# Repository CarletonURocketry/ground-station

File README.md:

# CUInSpace Telemetry Server

This software is a command line tool for retrieving UART data via serial from the CUInSpace
[ground station board][ground-station-board] and parsing it into readable data which is served via websocket for the
[ground-station-ui][ground-station-ui] live telemetry dashboard.

## Quick Start
Before starting, ensure you have Python 3.11+ installed and the CP210x driver for the homemade ground-station board UART
connection. This is not necessary if using the PICTail Daughter Board.

- Download the latest release
- Navigate to the project directory from the terminal
- Run `pip install -r requirements.txt`
- Run `py main.py -h` for a list of commands

Note that the ground station device should be connected before starting the telemetry server in order to receive an
accurate list of available serial ports.

## Further Reading
Please see the [GitHub Wiki][wiki] for further documentation on how to set up and run the telemetry server.

## Contribution
To contribute to this project, please view the contribution guidelines in the project's GitHub Wiki. Note that
contributions are currently limited to *Carleton University students or CUInSpace members*.

### Authors
- Samuel Dewan
- Thomas Selwyn
- Matteo Golin
- Arsalan Syed

<!--Links-->
[ground-station-board]: https://github.com/CarletonURocketry/avionics-hardware/pull/18
[ground-station-ui]: https://github.com/CarletonURocketry/ground-station-ui
[wiki]: https://github.com/CarletonURocketry/ground-station/wiki

## Installation
```
python3 -m venv .venv
```

```
source .venv/bin/activate
```

```
pip install -r requirements.txt
```

```
pip install -e .
```

## Running the ground station
```
python main.py
```

## Running the radio tests
### To receive
```
python range-test/receive.py
```
### To transmit
```
python range-test/transmit.py
```

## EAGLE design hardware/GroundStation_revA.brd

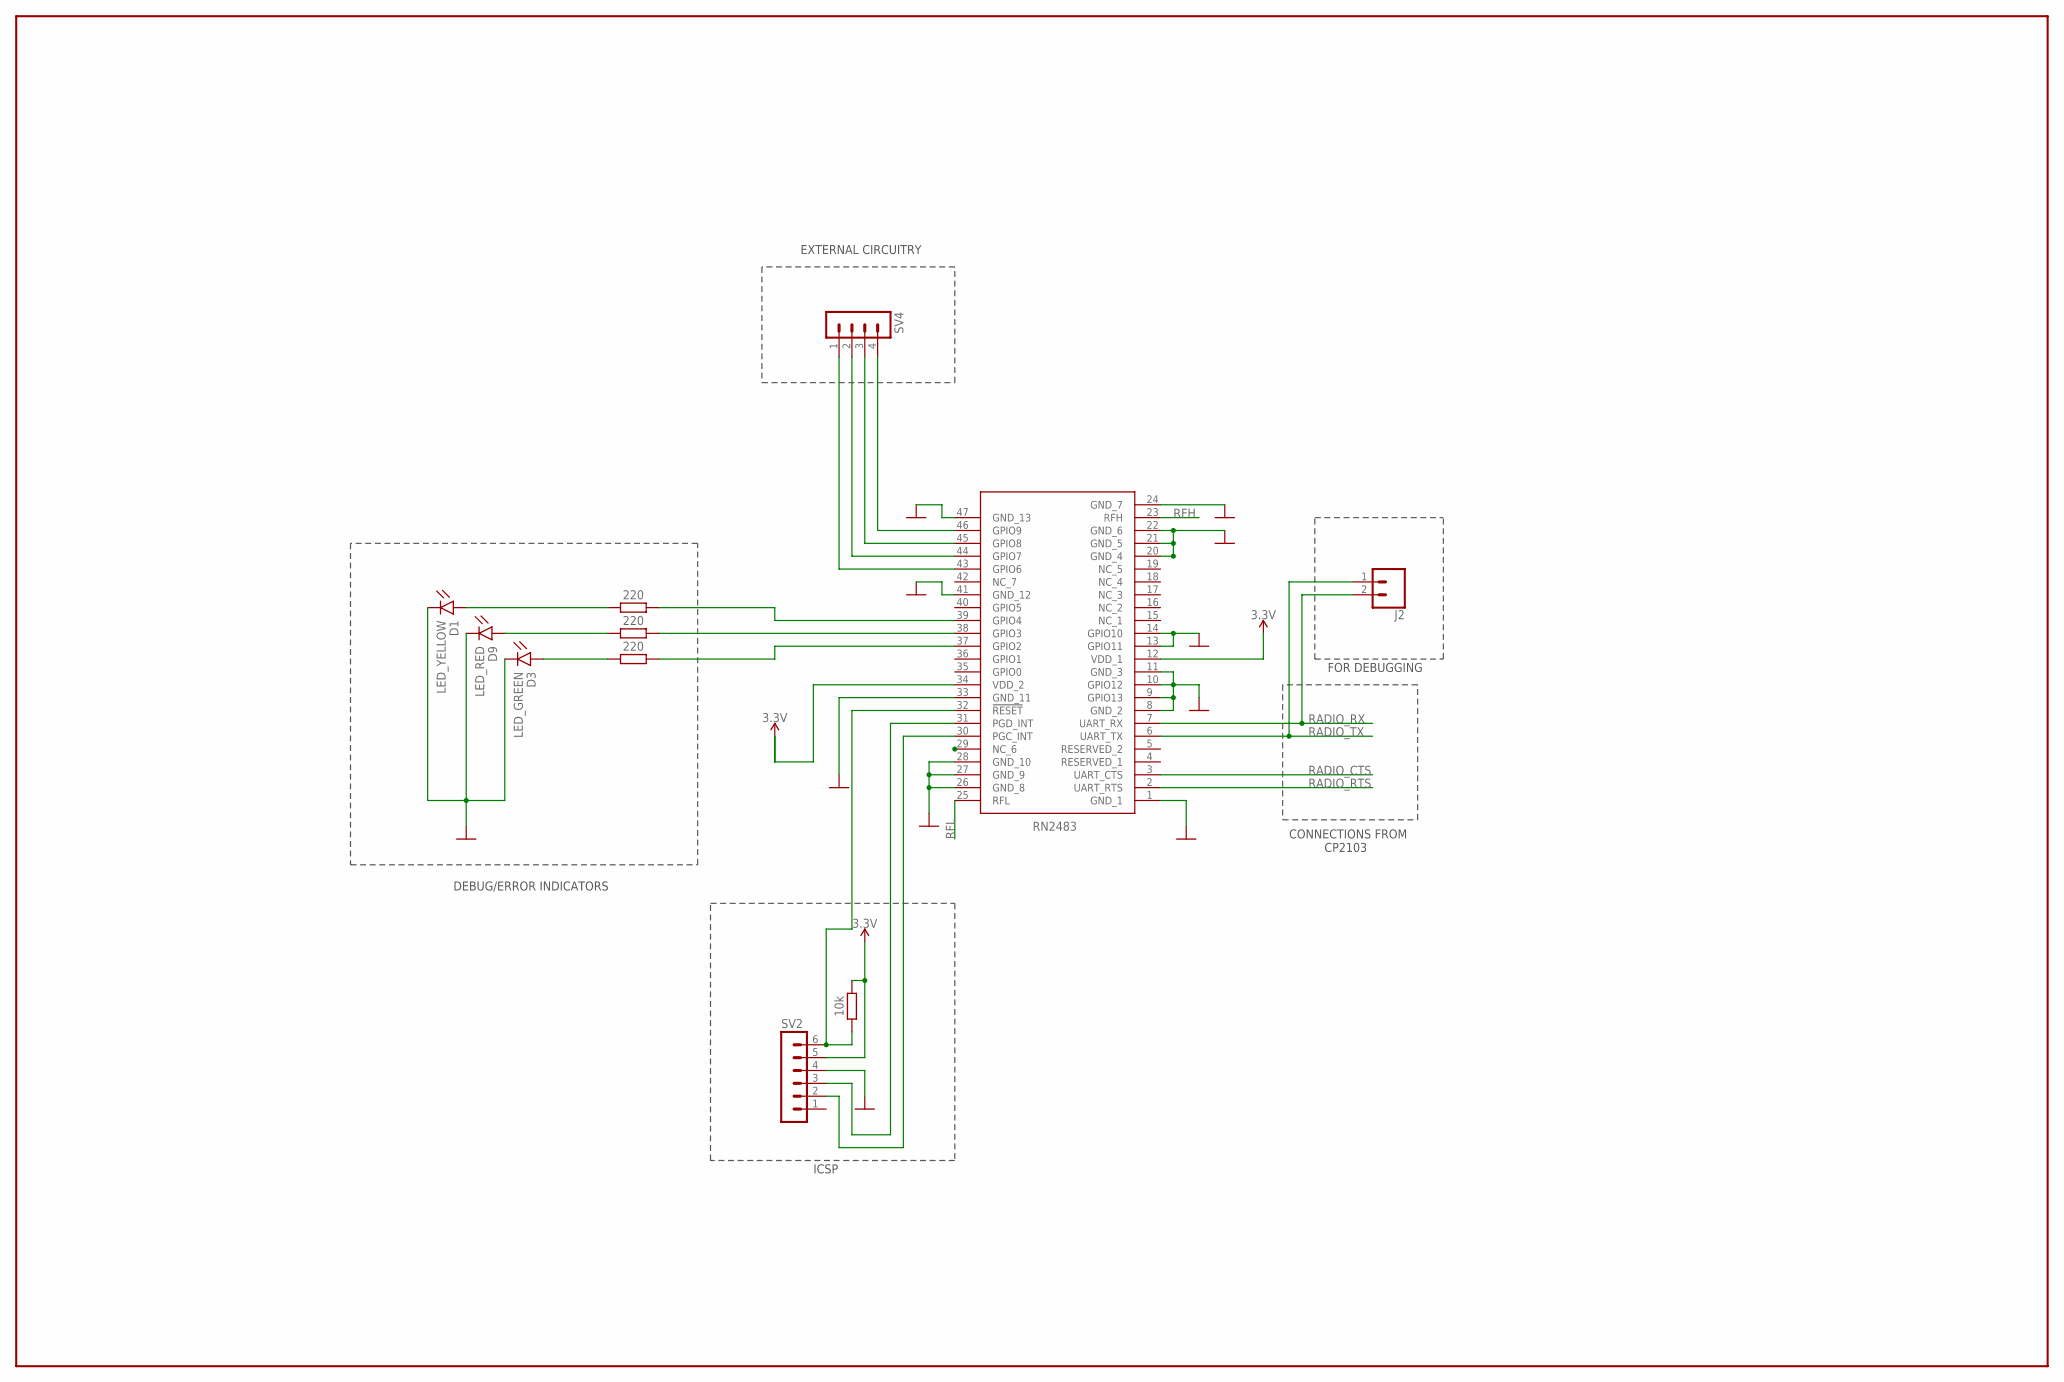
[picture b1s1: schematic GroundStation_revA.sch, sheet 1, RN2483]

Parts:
D1: LED_YELLOW; LEDC1608X55N_FLAT-Y
D3: LED_GREEN; LEDC1608X55N_FLAT-G
D9: LED_RED; LEDC1608X55N_FLAT-R
J2: CONN_02; 1X02
R12: 10k; RESC1608X60
R14, R15, R16: 220; RESC1608X60
RN2483: RN2483A-I_RM104; RN2483AIRM104
SV2: MA06-1
SV4: MA04-1

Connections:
3.3V: R12.1, RN2483.12 (VDD_1), RN2483.34 (VDD_2), SV2.5; also elsewhere on the board
D2: D9.A, R15.1
GND: D1.C, D3.C, D9.C, RN2483.1 (GND_1), RN2483.8 (GND_2), RN2483.9 (GPIO13), RN2483.10 (GPIO12), RN2483.11 (GND_3), RN2483.13 (GPIO11), RN2483.14 (GPIO10), RN2483.20 (GND_4), RN2483.21 (GND_5), RN2483.22 (GND_6), RN2483.24 (GND_7), RN2483.26 (GND_8), RN2483.27 (GND_9), RN2483.28 (GND_10), RN2483.33 (GND_11), RN2483.41 (GND_12), RN2483.47 (GND_13), SV2.4; also elsewhere on the board
GPIO_2: R14.2, RN2483.37 (GPIO2)
GPIO_3: R15.2, RN2483.38 (GPIO3)
GPIO_4: R16.2, RN2483.39 (GPIO4)
GPIO_6: RN2483.43 (GPIO6), SV4.1
GPIO_7: RN2483.44 (GPIO7), SV4.2
GPIO_8: RN2483.45 (GPIO8), SV4.3
GPIO_9: RN2483.46 (GPIO9), SV4.4
unnamed: D3.A, R14.1
unnamed: D1.A, R16.1
PCG_INT: RN2483.30 (PGC_INT), SV2.2
PGD_INT: RN2483.31 (PGD_INT), SV2.3
RADIO_CTS: RN2483.3 (UART_CTS); also elsewhere on the board
RADIO_RTS: RN2483.2 (UART_RTS); also elsewhere on the board
RADIO_RX: J2.2, RN2483.7 (UART_RX); also elsewhere on the board
RADIO_TX: J2.1, RN2483.6 (UART_TX); also elsewhere on the board
RFH: RN2483.23 (RFH); also elsewhere on the board
RFL: RN2483.25 (RFL); also elsewhere on the board
RN2483_RESET: R12.2, RN2483.32 (!RESET), SV2.6

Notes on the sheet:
ICSP
DEBUG/ERROR INDICATORS
EXTERNAL CIRCUITRY
CONNECTIONS FROM CP2103
FOR DEBUGGING

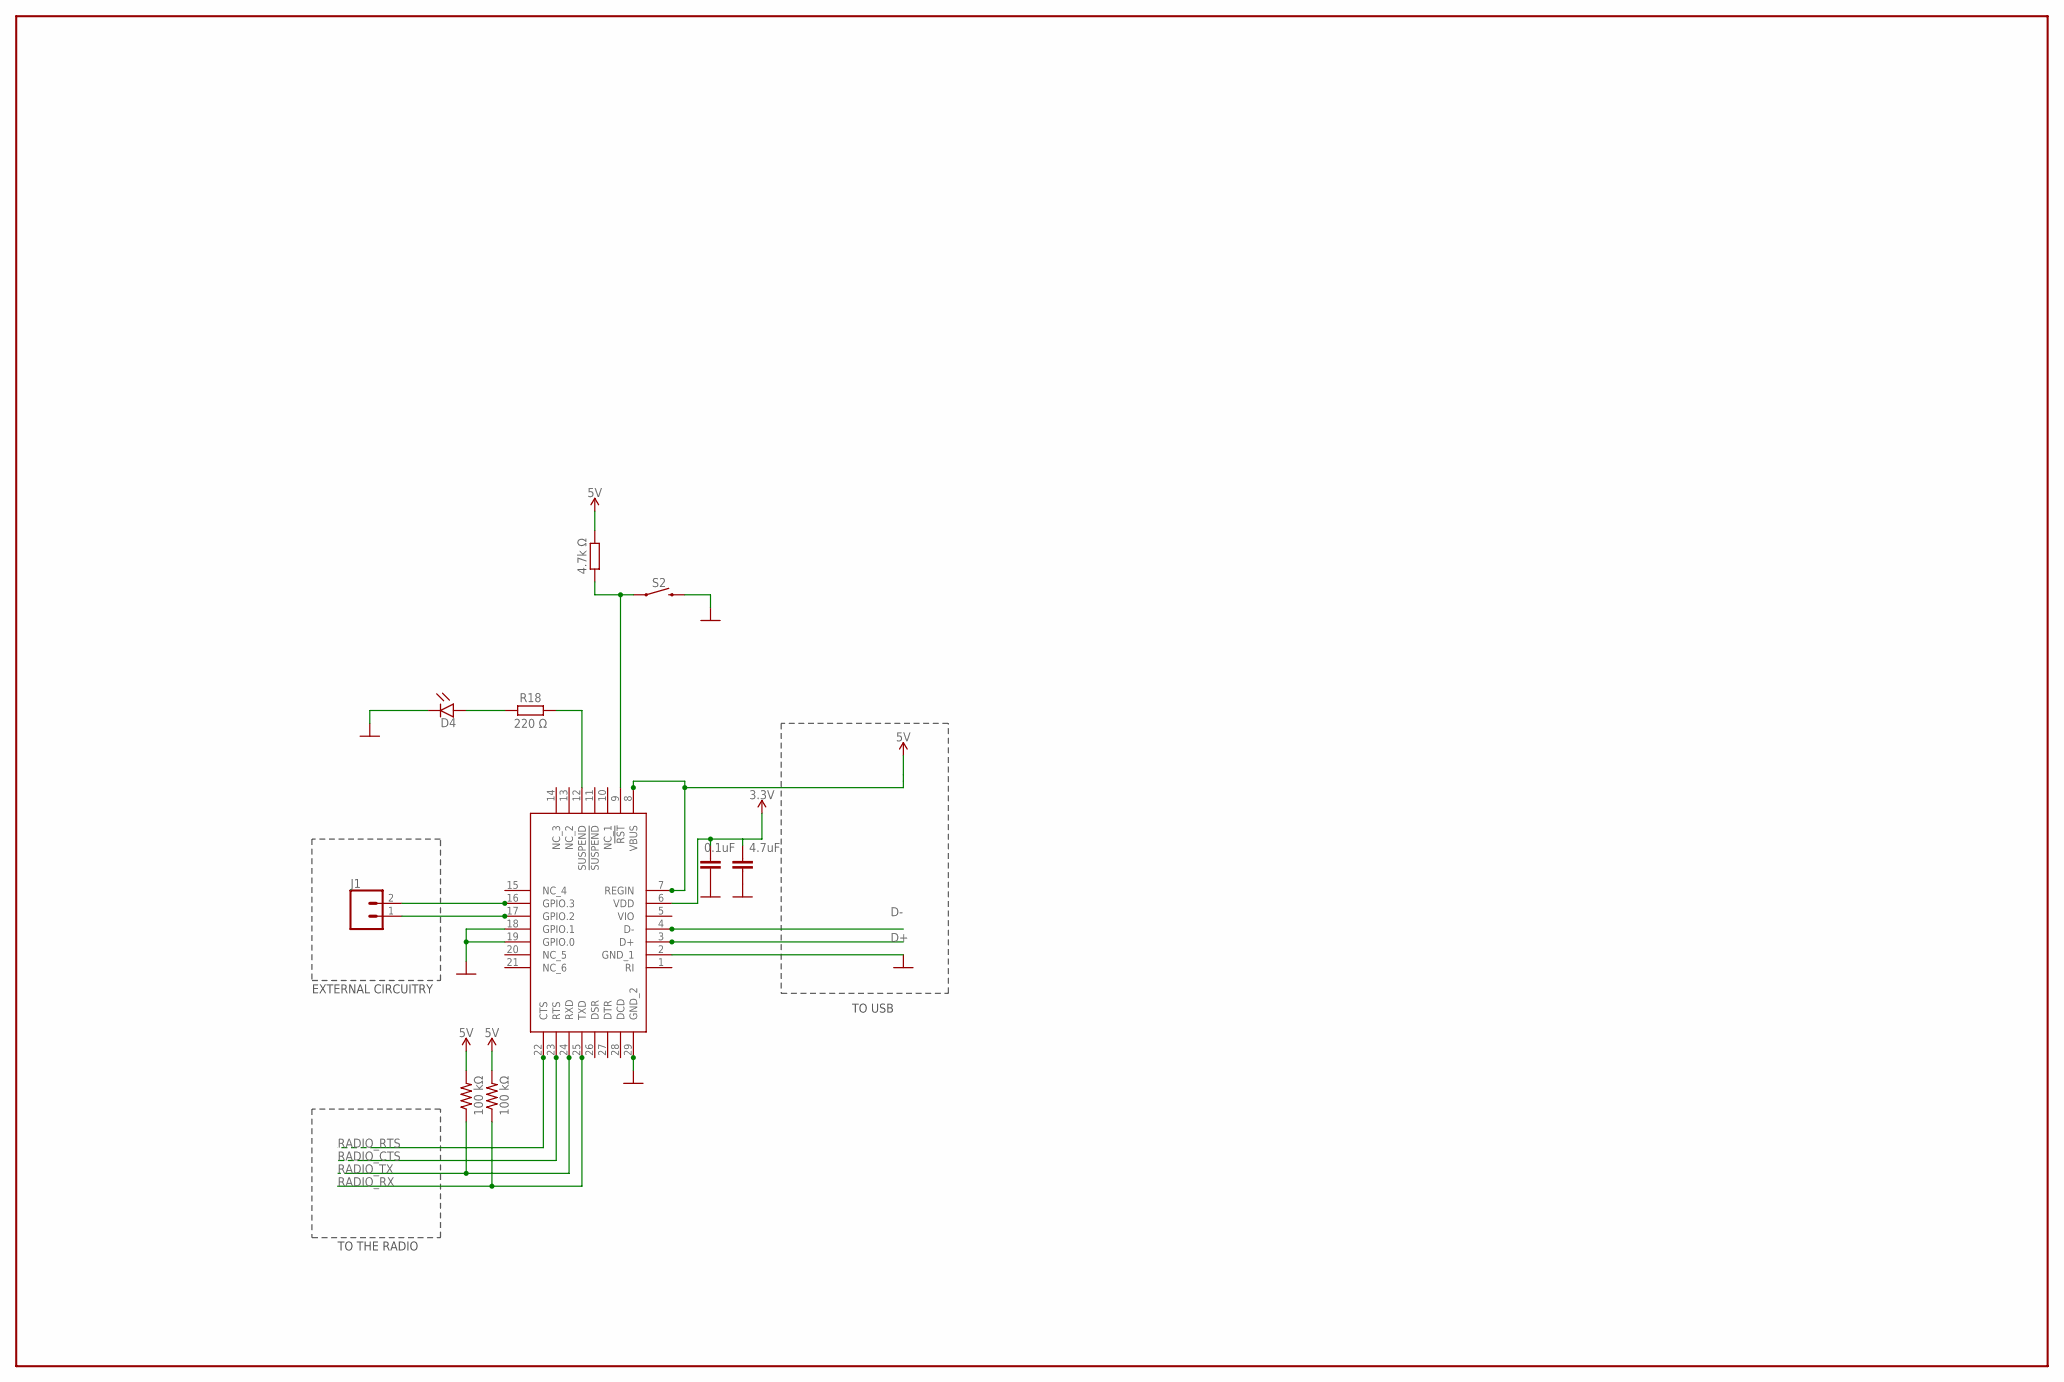
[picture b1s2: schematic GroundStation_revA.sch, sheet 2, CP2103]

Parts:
C7: 0.1uF; CAPC2012X110
C9: 4.7uF; CAPC2012X110
D4: LED_RED; LEDC1608X55N_FLAT-R
IC4: CP2103-GM; QFN50P500X500X100-29N
J1: CONN_02; 1X02
R1, R9: 100 kΩ; R0805
R17: 4.7k Ω; RESC1608X60
R18: 220 Ω; RESC1608X60
S2: MOMENTARY-SWITCH-SPST-PTH-6.0MM-KIT; TACTILE_SWITCH_PTH_6.0MM_KIT

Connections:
3.3V: C7.1, C9.1, IC4.6 (VDD); also elsewhere on the board
CP2103_GPIO2: IC4.17 (GPIO.2), J1.1
CP2103_GPIO3: IC4.16 (GPIO.3), J1.2
CP2103_RST: IC4.9 (!RST), R17.2, S2.1
D+: IC4.3 (D+); also elsewhere on the board
D-: IC4.4 (D-); also elsewhere on the board
GND: C7.2, C9.2, D4.C, IC4.2 (GND_1), IC4.18 (GPIO.1), IC4.19 (GPIO.0), IC4.29 (GND_2), S2.3 (2); also elsewhere on the board
unnamed: D4.A, R18.1
RADIO_CTS: IC4.23 (RTS); also elsewhere on the board
RADIO_RTS: IC4.22 (CTS); also elsewhere on the board
RADIO_RX: IC4.25 (TXD), R9.1; also elsewhere on the board
RADIO_TX: IC4.24 (RXD), R1.1; also elsewhere on the board
SUSPEND: IC4.12 (SUSPEND), R18.2
V_BUS: IC4.7 (REGIN), IC4.8 (VBUS), R1.2, R9.2, R17.1; also elsewhere on the board

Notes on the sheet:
TO THE RADIO
EXTERNAL CIRCUITRY
TO USB

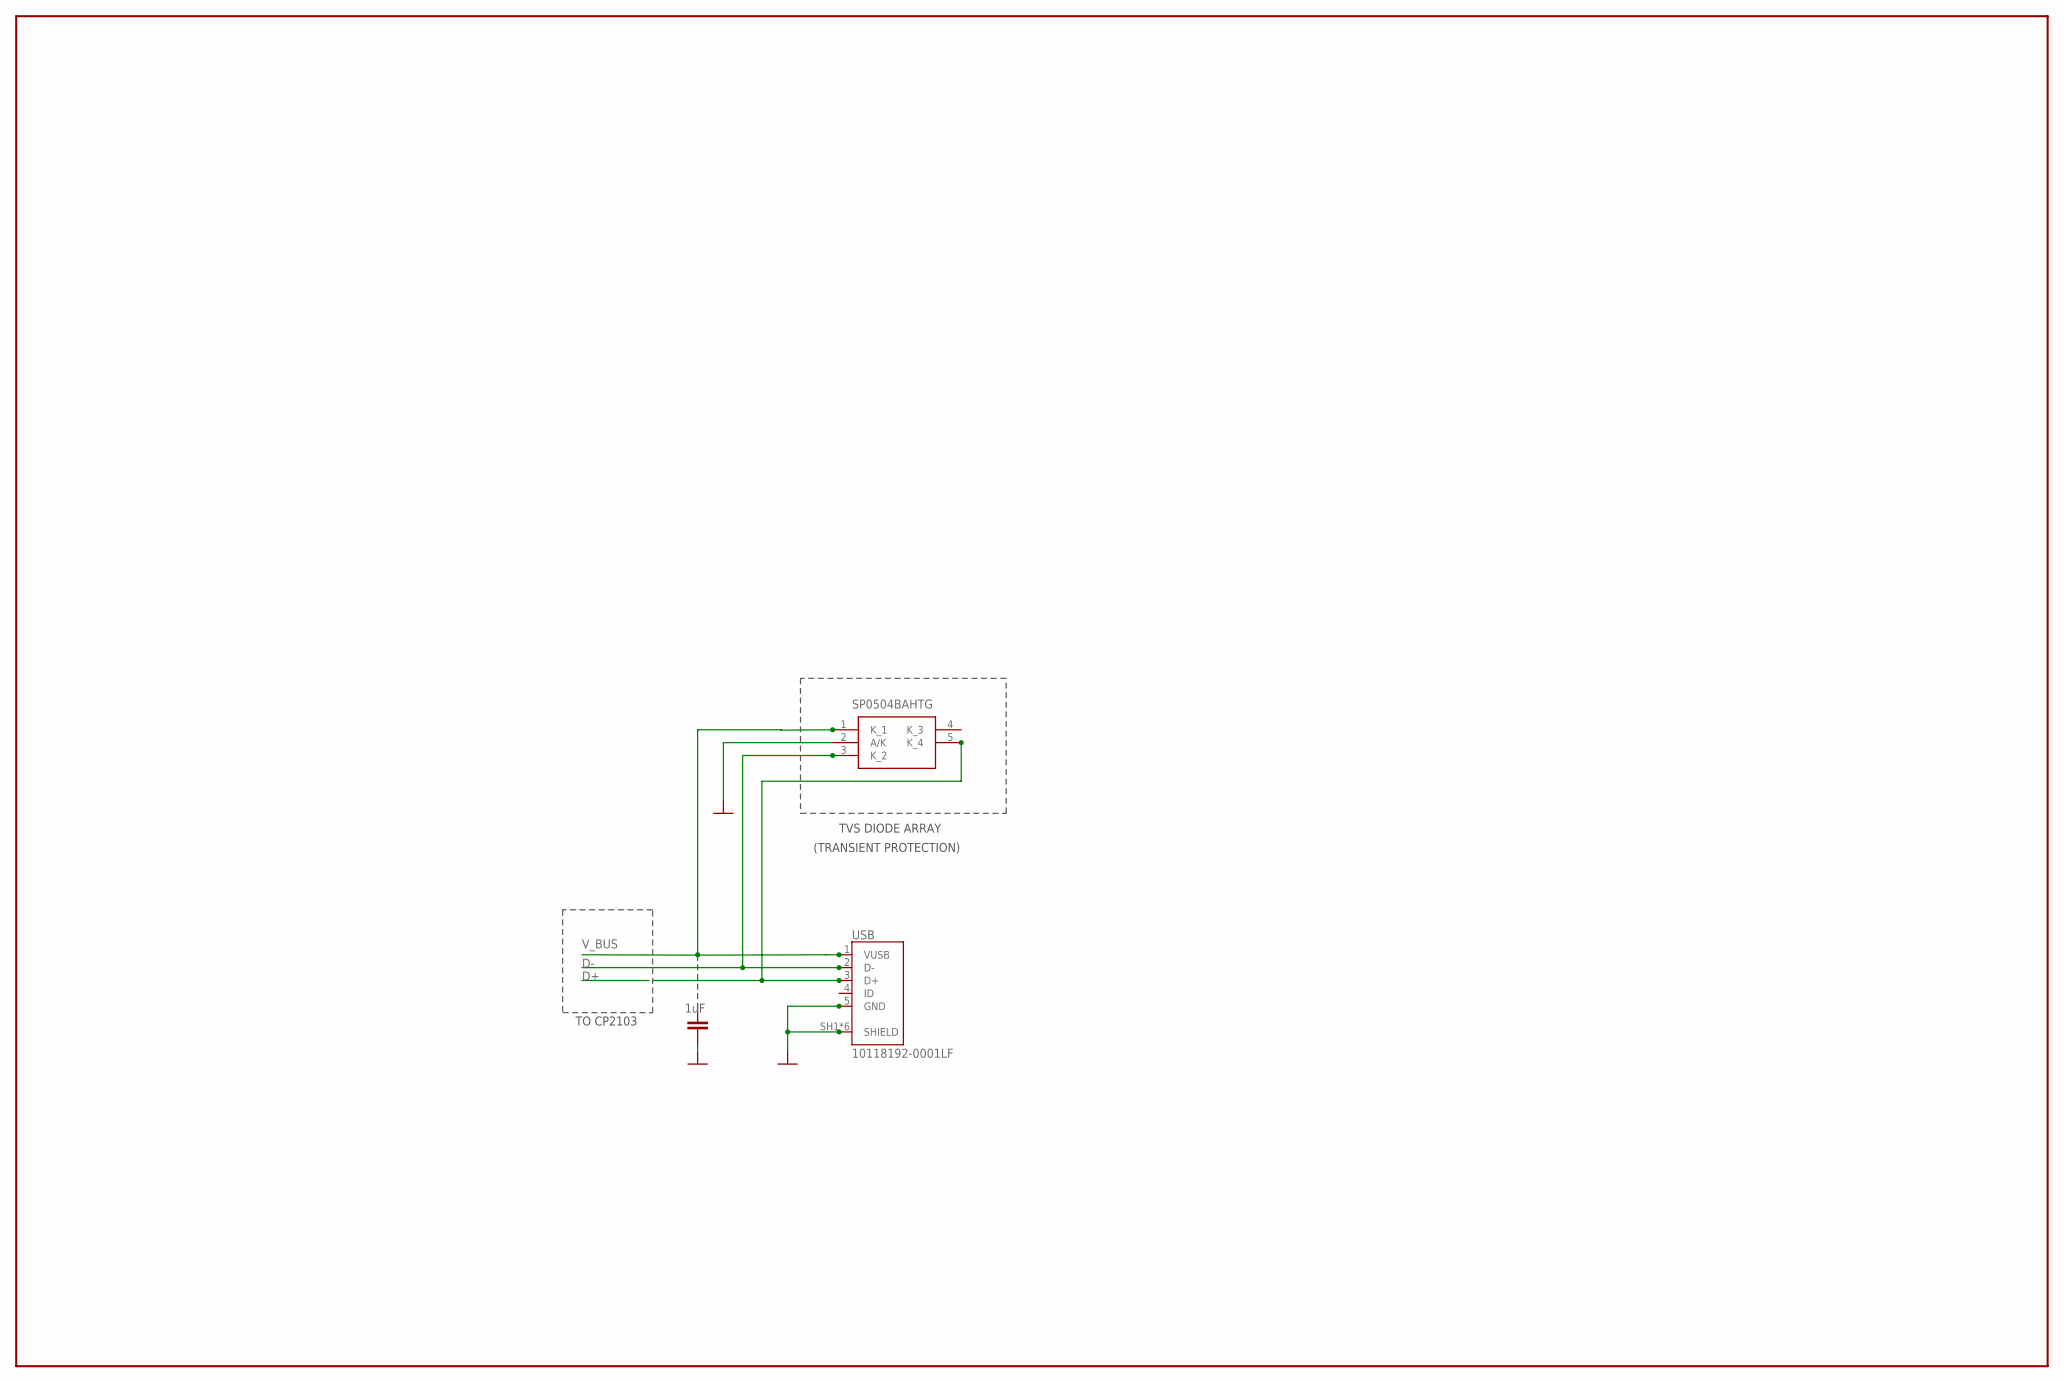
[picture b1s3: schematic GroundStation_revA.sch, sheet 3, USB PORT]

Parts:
C8: 1uF; CAPC2012X110
IC6: SP0504BAHTG; SOT95P280X145-5N
USB: 10118192-0001LF

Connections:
D+: IC6.5 (K_4), USB.3 (D+); also elsewhere on the board
D-: IC6.3 (K_2), USB.2 (D-); also elsewhere on the board
GND: C8.2, IC6.2 (A/K), USB.5 (GND), USB.SH1 (SHIELD), USB.SH2 (SHIELD), USB.SH3 (SHIELD), USB.SH4 (SHIELD), USB.SH5 (SHIELD), USB.SH6 (SHIELD); also elsewhere on the board
V_BUS: C8.1, IC6.1 (K_1), USB.1 (VUSB); also elsewhere on the board

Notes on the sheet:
TVS DIODE ARRAY
(TRANSIENT PROTECTION)
TO CP2103

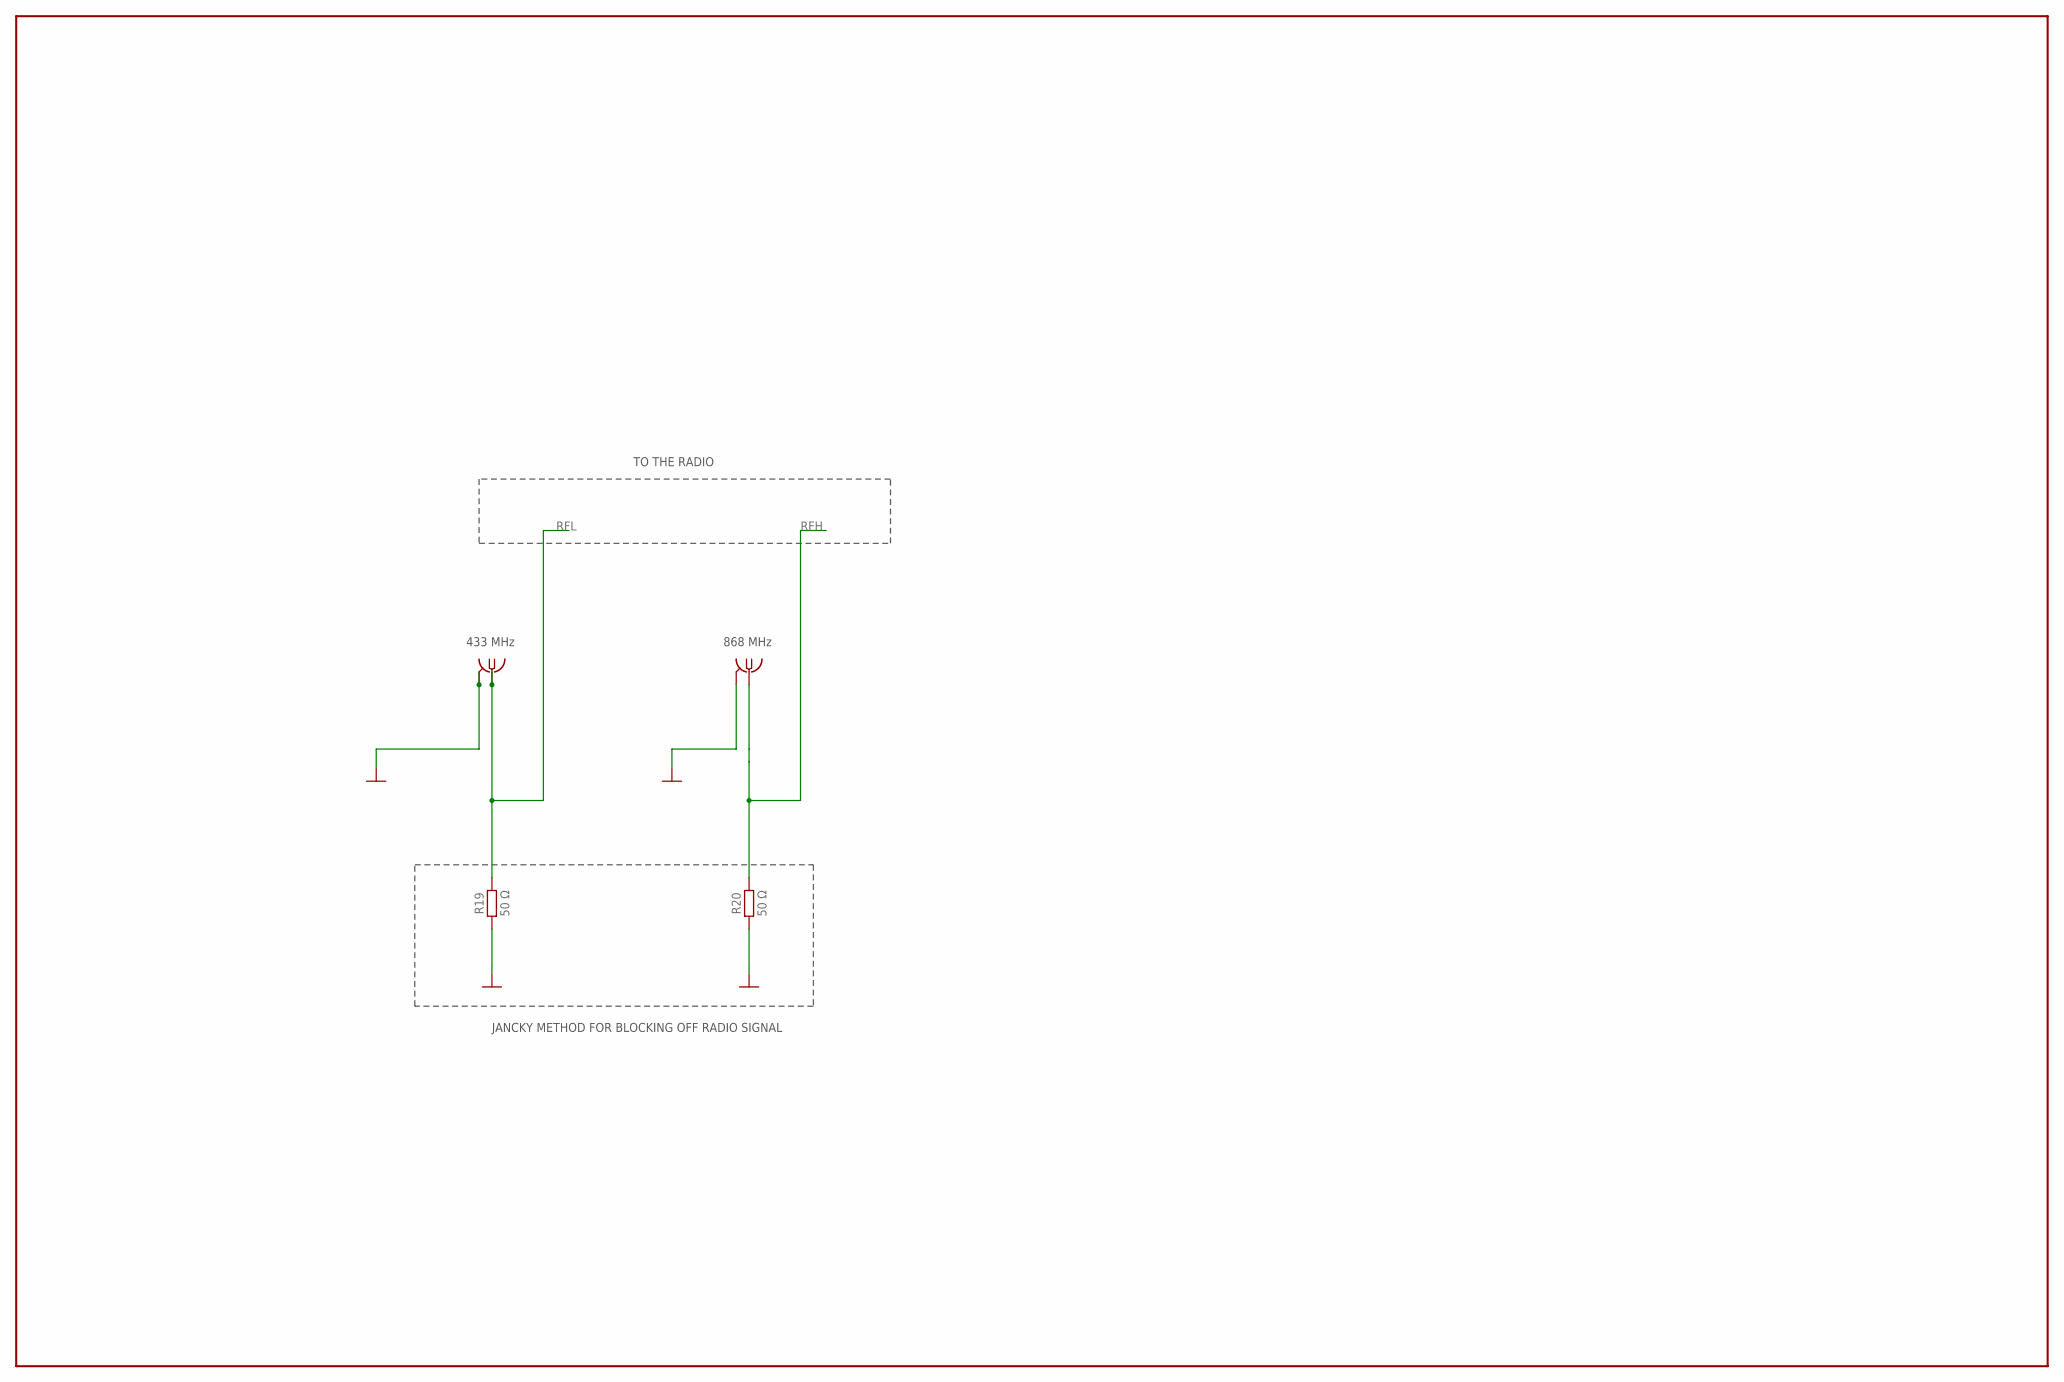
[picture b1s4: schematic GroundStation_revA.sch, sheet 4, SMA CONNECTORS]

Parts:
ANT1, ANT2: 5MMSMA
R19, R20: 50 Ω; RESC1608X60

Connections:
GND: ANT1.GND, ANT1.GND2 (GND), ANT2.GND, ANT2.GND2 (GND), R19.1, R20.1; also elsewhere on the board
RFH: ANT2.RF (1), R20.2; also elsewhere on the board
RFL: ANT1.RF (1), R19.2; also elsewhere on the board

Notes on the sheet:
433 MHz
868 MHz
JANCKY METHOD FOR BLOCKING OFF RADIO SIGNAL
TO THE RADIO

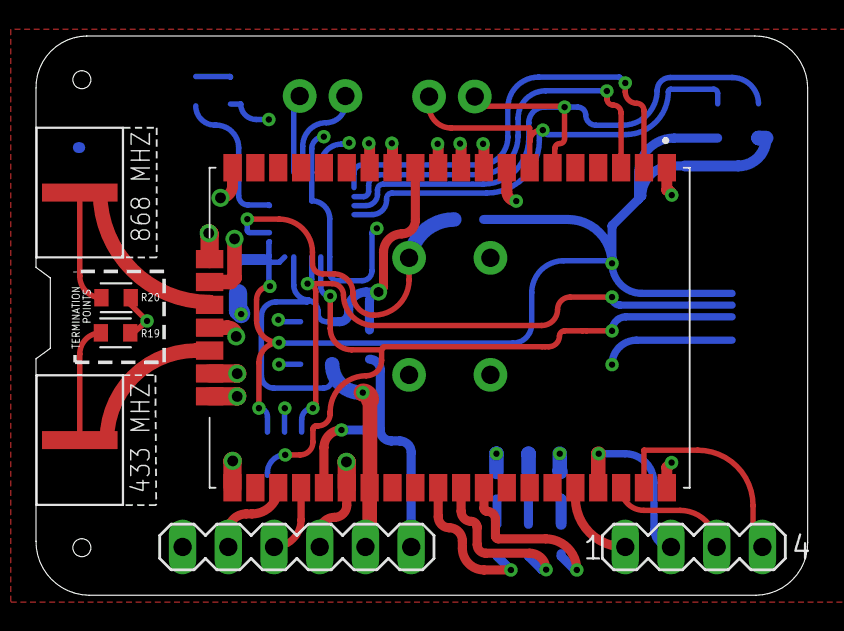
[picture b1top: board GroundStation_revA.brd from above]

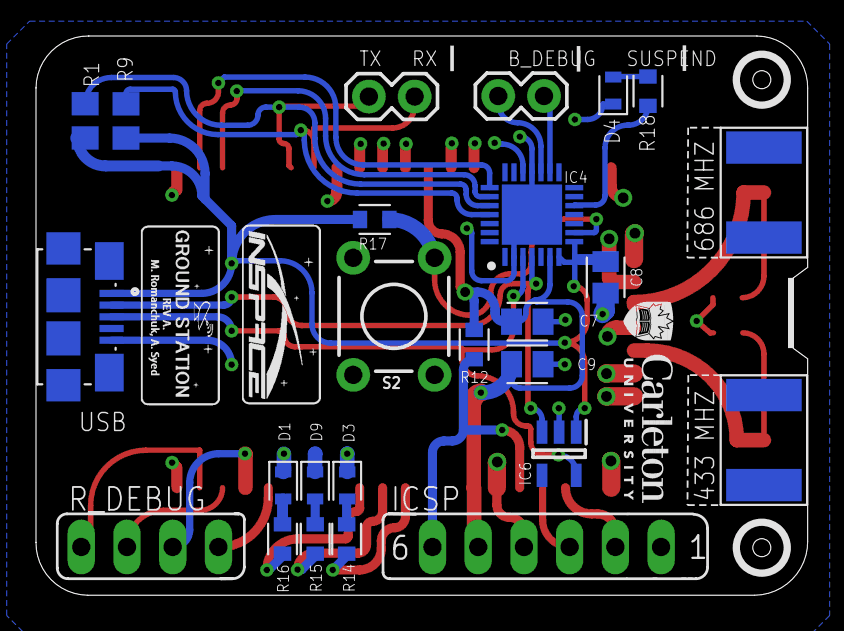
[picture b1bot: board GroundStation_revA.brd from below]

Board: 4 copper layers, 42.9 x 31.1 mm, 28 parts (21 on the bottom side), 29 nets.

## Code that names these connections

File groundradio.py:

# Ground station software for communication with the CU-InSpace rocket via an
# RN2483 LoRa radio module.
# Authors:


import serial


ser = serial.Serial( port = "COM4",
                        timeout=1,
                        baudrate=57600,
                        # number of bits per message
                        bytesize=serial.EIGHTBITS,
                        # set parity check: no parity
                        parity=serial.PARITY_NONE,
                        # number of stop bits
                        stopbits = 1,
                        # disable hardware (RTS/CTS) flow control
                        rtscts=False)   

def init_serial(port):
    
        
    return 0
    


def init_GPIO():
    write_to_ground_station("sys set pinmode GPIO0 digin")
    write_to_ground_station("sys set pinmode GPIO1 digin")
    write_to_ground_station("sys set pinmode GPIO2 digin")
    write_to_ground_station("sys set pinmode GPIO3 digin")
    write_to_ground_station("sys set pinmode GPIO4 digin")
    write_to_ground_station("sys set pinmode GPIO5 digin")
    write_to_ground_station("sys set pinmode GPIO6 digin")
    write_to_ground_station("sys set pinmode GPIO5 digin")
    write_to_ground_station("sys set pinmode GPIO6 digin")
    write_to_ground_station("sys set pinmode GPIO7 digin")
    write_to_ground_station("sys set pinmode GPIO8 digin")
    write_to_ground_station("sys set pinmode GPIO9 digin")
    write_to_ground_station("sys set pinmode GPIO10 digin")
    write_to_ground_station("sys set pinmode GPIO11 digin")
    write_to_ground_station("sys set pinmode GPIO12 digin")
    write_to_ground_station("sys set pinmode GPIO13 digin") 
     

def init_ground_station():


    # initlize all the pins to be inputs
    init_GPIO()

# set the frequency of the radio
    radio_set_freq(433050000)
    
    # # set the power to -14 db
    radio_set_pwr(14)
    
    # # set the spreading factor
    radio_set_sf("sf9")
    
    # # set the coding rate
    radio_set_cr("4/7")
    
    # # set bandwdith
    radio_set_bw(500)
    
    # # set prlen preamble length
    radio_set_prlen(6)
    
    # # set crc
    radio_set_crc("on")
    
    # # set iqi
    radio_set_iqi("on")
    
    # # set sync word to be 0x43
    radio_set_sync("43")
    
    # print("sucessfully configured lora radio")


    
def write_to_ground_station(command_string): 
    """writes data to the ground station via UART
       author: Tarik
       @param command_string: full command to be send to the ground station
       @param COM_PORT: the COM port to be used for the UART transmission
       
       Ex. 
       >>write_to_ground_station("radio set pwr 7", COM1)
       >>"ok"
       
       //above example sets the radio tramission power to 7 using COM1
       
       """
    
    data = str(command_string) 
    
    #must include carriage return for valid commands (see DS40001784B pg XX)
    data = data + "\r\n"
    
    # encode command_string as bytes and then transmit over serial port
    ser.write(data.encode('utf-8'))  
    
    #if ground station produces error in response to command then it will
    #halt the program
    flag =wait_for_ok()
    
    #if ground station produces error in response to command then it will
    #halt the program
    return flag
    
def read_from_ground_station(register: int):
    """reads data from the ground station via UART and puts it into the
    correct data format to be passed onto the UI (check the logging format)
    author: elias
    @param  register: address of register to read from
    @return data: the data that is stored in that register
    """


def load_map():
    """load in a map that can be used offline
        author: """

# wait for serial response we have set a timeout value so it will wait for a response and checks if it's not ok

def wait_for_ok():
    # flush the serial port
    ser.flush()
    
    #read 'ok' from the terminal, if it's there.
    rv = str(ser.readline())
    #printtoUI(rv)
    
    if ('ok' in rv):  # check for ok and report if param invalid
        print('success', rv)
        return True
    
    elif rv != 'ok':
        print("ERROR: wait for ok(): " + rv)
        return False
def printtoUI(rv):
    return rv
    

    

def radio_set_freq(freq):
    
    #frequencies = [250000, 125000, 62500.0, 31300.0, 15600.0, 7800.0, 3900.0,
    #              200000, 100000, 50000, 25000, 12500.0, 6300.0, 3100.0,
    #             166700.0, 83300.0, 41700.0, 20800.0, 10400.0, 5200.0, 2600.0]
    #if freq in frequencies:
    
    success = write_to_ground_station("radio set freq " + str(freq))
    if(success):
        print("frequency sucessfully set")
        return True
    else:
        print("error: frequency not set")
        return False
            

# set power possible values between -3 and 14 db
def radio_set_pwr(pwr):
    if pwr in range(-3, 15):
        sucess=  write_to_ground_station("radio set pwr " + str(pwr))
        if sucess:
            print("value power sucessfully set")
        else:
            print("power error:radio unable to set")
    
# set spreading factor can only be set to  sf7", "sf8", "sf9", "sf10", "sf11", "sf12"]


def radio_set_sf(sf):
    if sf in ["sf7", "sf8", "sf9", "sf10", "sf11", "sf12"]:
        sucess= write_to_ground_station("radio set sf " + sf)
        if sucess:
            print("value spreading factor sucessfully set")
        else:
            print("spreading factor  error:radio unable to set")
    
# set coding rate which can only be "4/5", "4/6", "4/7", "4/8"


def radio_set_cr(cr):
    if cr in ["4/5", "4/6", "4/7", "4/8"]:
        sucess=write_to_ground_station("radio set cr " + str(cr))
        if sucess:
            print("value cr sucessfully set")
        else:
            print("cr error:radio unable to set")
   

# set the bandwidth which can only  be 125 250 or 500 hz


def radio_set_bw(bw):
    if bw in [125, 250, 500]:
        sucess= write_to_ground_station("radio set bw " + str(bw))
        if sucess:
            print("value bw sucessfully set")
        else:
            print("bw error:radio unable to set")
    

# set IQI to be on or off


def radio_set_iqi(iqi):
    if iqi in ["on", "off"]:
        sucess= write_to_ground_station("radio set iqi " + str(iqi))
        if sucess:
            print("value sucessfully set")
        else:
            print("iqi error:radio unable to set")
    
# set sync word it's a 2 bytes no error checking is done because it's confusing to change between types


def radio_set_sync(sync):
    sucess= write_to_ground_station("radio set sync " + str(sync))
    if sucess:
        print("value sync word sucessfully set")
    else:
        print("sync param error:radio unable to set ")


# set the preamble length between 0 and  65535
def radio_set_prlen(pr):
    if pr in range(0, 65535):
        sucess=write_to_ground_station("radio set prlen " + str(pr))
        if sucess:
            print("value prlen sucessfully set")
        else:
            print("prlen error:radio unable to set ")
    

# crc can only be set to True or false to enable error checking


def radio_set_crc(crc):
    if crc in ["on", "off"]:
        sucess= write_to_ground_station("radio set crc " + str(crc))
        if sucess:
            print("value crc sucessfully set")
        else:
            print("crc error:radio unable to set")
    

def radio_set_rxmode():
    # set the timeout to 65535 the maximum amount
    # we will set this value to be the transmission
    #The mac pause command must be called before any radio transmission
    #or reception, even if no MAC operations have been initiated before.
    #TODO : set a timeout for recieving 
    
    write_to_ground_station("mac pause")

    write_to_ground_station("radio set wdt 0")

    # set rx amount to the amount of bytes we need
    #suggestion is to keep it to 0 since we know the packet lenght and anoumt of blocks is varible
    write_to_ground_station("radio rx 0")
def test_radio():
    #send a valid command which get's the frequency
        write_to_ground_station("radio set wdt 5")

        #write_to_ground_station("radio tx 48656c6C6F")
        
def radio_set_txmode(data):
    
    #must pause mac, even if not used
    write_to_ground_station('mac pause')
    
    #must stop radio from reciving 
    write_to_ground_station('radio rxstop')
    
    #send the data
    write_to_ground_station("radio tx 48656c6C6F"+data)
    
    return ser.readline()

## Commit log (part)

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2024-02-03 Added altitude DB decoding and more
2024-02-03 Added AltitudeDB parsing and other small fixes
2024-02-03 Add VE3LWN call sign
2024-02-04 Read faults key from config.json
2024-02-08 Fixes e203 flake8 warnings by following best practice throughout project
2024-02-08 Structured faults system to how I want it, fixed pyright errors, and almost finished thresholds config system
2024-02-08 Fix rocket thresholds type annotation
2024-02-08 Updated stock websocket json have telemetry keys in lists
2024-02-08 Implemented a filehandler in tornado and better error handling if port is already in use.
2024-02-08 Reduce trailing periods to line up with artwork
2024-02-12 Added test data from the new packetsv1 packager instance. This should allow some marginal testing.
2024-02-12 Corrected update mission list startup error
2024-02-13 Passed version through to replay system to change output logic
2024-02-13 Replay now plays V1 test mission so we can start working on parsing
2024-02-14 Run linter
2024-02-14 Closes #67: Changed spin loops to block thread on queues to have items, added sleep to telemetry spin loop as temp fix
2024-02-14 Print BlockHeader instead of just length
2024-02-14 Updated PacketHeader for V1
2024-02-14 Added V1 packet header tests
2024-02-15 Updated V1 block decoding and now parse implemented data blocks
2024-02-15 Throws v1 packets into telemetry data buffer
2024-02-15 Remove old parse payload function
2024-02-20 Add correct declaration for sigterm funcs
2024-02-21 Renamed class to be less verbose.
2024-02-21 Updated RN2483 class to require one less method for writing to the radio.
2024-02-21 Added a link to the datasheet to the code.
2024-02-24 Move telemetry related errors to their own file
2024-02-24 RN2483 controller works but only outside of a Process thread. Not sure why.
2024-02-24 Set a longer timeout for read operations; receives now consistently return data.
2024-02-24 Move packet header validation into its own function
2024-02-24 Fix telemetry blocks not being added as dicts
2024-02-25 Removed unnecessary process inheritance. Made rn2483 radio process a function, since that is effictively what the class was.
2024-02-25 Fix some typing issues
2024-02-25 Radio now reliably receives each transmitted message.
2024-02-25 Formatting.
2024-02-25 Move external functions and dataclasses to telemetry_utils
2024-02-25 Fix typing errors and comments
2024-02-26 Replay now works without SD card. Lots of dead code to be removed and refactored, but replay currently works.
2024-02-26 Add some todos, remove unnecessary Process inheritance.
2024-02-26 Fixed failing tests.
2024-02-27 Add full telem test file
2024-02-27 Run formatter
2024-02-28 Fix shutdown sequence
2024-02-28 Fixed altitude data block decoding to account for altitude being sent in mm.
2024-02-28 Lint
2024-02-29 Test data updated! Now includes real mission timestamps and altitude data.
2024-02-29 Fix sillyness
2024-03-06 Outputs values as array to websocket
2024-03-06 Clear packet buffer fully on telemetry reset
2024-03-07 Fixed
2024-03-09 added docstrings
2024-03-10 Finish new output json
2024-03-10 Fixed flake formatting
2024-03-11 Resolves issue with 2 or more subkeys. dict.fromkeys(keys, []) makes [] all point to the same object. Oh, python...
2024-03-11 Ensures new stored_value dict is properly initialized upon clear (dict.fromkeys(key, []) points all keys to same object) Remove all uses of dict.fromkeys() from packet file
2024-03-12 Corrected dataclass issues and converter docstrings
2024-03-12 Removed unnecessary class attributes.
2024-03-12 Update block header tests
2024-03-12 Remove v0 block
2024-03-13 test for random subtype ValueError
2024-03-13 Added all test cases function covers
2024-03-13 Add all test case relevant to the function
2024-03-14 ['mission_time']
2024-03-15 Resolve some errors
2024-03-16 Fix json packets
2024-03-16 Remove v0 data blocks
2024-03-16 FIx jsp imports
2024-03-16 fix flake8
2024-03-17 Remove redundant tests
2024-03-17 Fix flake
2024-03-23 Have packet throw error if version is unsupported
2024-03-23 Fixed the parse function such that it raises NotImplementer error when encountered with subtype that are know yet not implemented
2024-03-23 Fix block header tests
2024-03-23 Fix telemetry utils
2024-03-26 NotImplementedError implemented when subtype is None
2024-03-26 raised the exception ValueError
2024-03-26 caught the ValueError with a bad subtype
2024-03-27 fixed redundancy
2024-03-27 fixed redundancy again
2024-03-29 Tests for parse_radio_block have been added
2024-03-30 added parameter
2024-04-02 unraise the exceptions and reverse the order of them exceptions
2024-04-02 tested the exceptions for parse_radio_block
2024-04-06 renamed is_valid_packet_header to is_approved_packet_header, and made it return None instead of a boolean
2024-04-06 changed the test since the is_valid_packet_header also changed
2024-04-08 changed the name to from_approved_callsign and returned its functionality as before
2024-04-08 removed redundant code that was on parse_rn2483_transmission
2024-05-16 Add datablock parsing for lin acceleration and angular velocity
2024-05-16 Change invalid header tests to just call packet header constructor
2024-05-16 Fix not implemented test to try subtype that is not implemented
2024-05-16 Add tests for linear acceleration and angular velocity data blocks
2024-05-18 Fixed JSON serialization to accomodate new data types.
2024-05-19 Fixed failing test cases.
2024-05-19 Increasing the timeout avoids the problem with receiving 45 in quick succession.
2024-05-20 Make magnitude calculations work with absolute values
2024-05-20 Add a much longer test mission
2024-05-20 Change type defs to float
2024-05-25 Mistake in dictionary keys.
2024-05-25 Fixed decoder error with magnitude key.
2024-05-26 Change some info logging to debugs
2024-05-27 Refactor error handling to more correctly describe when errors occur
2024-06-04 New mission file with voltage data for testing.
2024-06-04 Update web socket format
2024-06-04 Add voltage db test
2024-06-06 Add coordinates data block and organize
2024-06-06 Add test for humidty block
2024-06-06 Change coordinates from millidegrees to degrees
2024-06-08 Decode coordinate DB to degrees.
2024-06-10 Include ACM* usb devices in available ports.
2024-07-09 Fix upgrade command in docker file prompting
2024-07-25 Move commands.py to telemetry module
2024-07-25 Fix some tests
2024-07-26 Remove telemetry prefix from file names
2024-08-07 Bump ground-station version
2024-08-07 Clean up some utils and rename file
2024-11-18 Add new packet format
2025-01-27 fix parsing
2025-03-13 Update radio parameters
2025-03-17 Update config name
2025-03-17 Add prelim basic auth
2025-03-22 Cleanup stuff for recording
2025-03-22 Start migrating packet spec
2025-03-22 Start working on parsing
2025-03-22 fix comment
2025-03-24 Add parsing hex
2025-03-24 add utility for converting to mission format
    * the files that are logged on the flight computer are in a different
    format than the replay system requires
    * added a way to convert into mission file format so logged files
    can be played back too
2025-03-25 generalize block parsing and types
    * used a more dynamic approach for block parsing so we could get
    access to more useful data elsewhere
2025-03-25 go back to using dataclasses for blocks
    * combined the newer method with dataclasses to get benefits of both
2025-03-27 Add deauthentication
2025-03-27 Fix header data parsing
2025-03-28 rip out decoder, replace with boring list
    * renamed the telemetry buffer class to reflect what it actually does
    * removed the decoder, blocks are now directly responsible for deciding
    where their measurements end up
2025-03-31 fix imports and types
2025-03-31 Separate launch and sea level alt and fix mission times
2025-03-31 Add more error catching
2025-04-01 add mission that follows new spec
2025-04-02 Remove creation of virtual environment and fix order of commands
2025-04-02 Add necesarry unit conversions
2025-04-04 Rebase
2025-04-04 Fix telemetry output dict
2025-04-05 Add linear acceleration and voltage to data output
2025-04-05 Remove debug logs
2025-04-30 Add rules to ignore star imports
2025-04-30 Fix some formatting issues
2025-04-30 Update requirements
2025-04-30 Update rocket name
2025-04-30 Remove syncword from testing until it's confirmed to be working
2025-04-30 The linter can bite me
2025-05-06 Add magnetometer block
2025-05-07 Remove telem packet json file
2025-05-13 Fix radio params to match inspace-nxtelem
2025-05-13 Fix packet timestamp parsing
2025-05-14 Fix blocks parsing timestamps as unsigned shorts
2025-05-14 Fix radio config tests
2025-05-14 Fix pyright errors
2025-05-15 Start adding BufferedWriter for recording
2025-05-15 Add some logs to authenticatiion process
2025-05-15 Fix auth logic
2025-05-15 Fix stupid rebasing issues
2025-05-15 Fix replay typing
2025-05-15 typing fixes 2
2025-05-15 Always convert websocket messages to strings
2025-05-15 Fix some packets not being parsed as signed ints
2025-06-14 Begin adding csv writer stuff and fix coord conversions
2025-07-17 Ignore typing
2025-07-17 Fix new flake8 issues
2025-07-23 Updated block_header tests
2025-08-08 Adding packet parsing for status and error
2025-08-15 Remove mentions of parsing, add missing field
2025-08-16 Add mission with error and status blocks
2025-08-23 Add El Blasto flight data
2025-09-20 add csv_converter.py
2025-10-18 moved the radio range test scripts to this repository
2025-10-18 added docs on running range test
2025-10-18 Moved config to range-test dir
2025-10-18 pytest now passes
2025-11-11 Fixed hosting address so the frontend can actually connect to it on CU-Wireless
2025-11-12 Removed auth system
2025-11-25 the ground station backend should not be as cmoplex as it is right now
2025-11-26 Can get radio packets over websocket
2025-11-28 Start/stop
2025-11-29 Write recordings. Some TODOs though.
2025-11-29 Make mission name the timestamp
2025-11-29 Flush
2025-11-29 Record
2026-01-10 Make mission name mandatory in function
2026-01-10 Return intead of raising exceptions
2026-01-15 black
2026-01-15 blacked again
2026-01-18 added api stuff for replay starting and stopping
2026-01-29 removed very annoying spammy logs
2026-02-02 Change to client_id instead of X-Client-ID
2026-02-05 Corse
2026-02-12 Added scripts to parse flight computer logs + some data
2026-02-13 fix seeking functionality
2026-03-01 Range scripts using old configs
2026-03-01 Added data as transmitted from josh
2026-03-01 Remove uneeded function
2026-03-02 Renamed josh output to usable name
2026-03-02 Added command line flag to play radio packets in loop from the recording
2026-03-02 Radio Scanning
2026-03-02 Implemented packet separation and artificial latency system
2026-03-02 Added comments to clarify the use of the timeline classes
2026-03-02 Unifying async workers and providing cancellation helpers
2026-03-02 Rm /client_id API route
2026-03-02 Check if /dev directory exists
2026-03-02 Removed fake packet creation flag
2026-03-03 Added transmission delay and QOL to range test scripts
2026-03-30 Implemented transmission of fake packet and sim of el blasto
2026-04-06 Logging block data in receive range test
2026-04-06 Removing old and putting new call signs ins
2026-05-02 Added path to list all recordings
2026-05-02 Stop replay from always looping
2026-05-02 Added featherweight el blasto data for replay
2026-05-04 Stitched cots and srad el blasto data together
2026-05-09 Integrated radio auto discovery in range test scripts
2026-05-09 Moved log-parser to general data-processing directory
2026-05-09 Putting back altitude above sea level into recording, was removed by accident
2026-05-09 Simplified timeline data artificial delaying logic
2026-05-09 Removed and added logs

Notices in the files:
README.md:
License: MIT
parts and their libraries:
SparkFun-Switches: Licensing: Creative Commons ShareAlike 4.0 International - https://creativecommons.org/licenses/by-sa/4.0
